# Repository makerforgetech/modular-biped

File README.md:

# Open Source, 3D Printable, Modular Robot Project

The **Modular Robot** project aims to educate and inspire individuals interested in robotics and electronics. This open-source initiative focuses on creating a fully autonomous companion robot with a variety of advanced features.

## Key Features

- **Control Systems**: Utilizes Arduino and Raspberry Pi, managed through custom PCBs.
- **Modular Body**: Configurable body components allow for easy customization and adaptability.
- **Software Modules**:
  - Animation: Handles the animation of the robot, including walking, turning, and other movements.
  - Braillespeak: Converts text to Braille and speaks it using a proprietary audio output using the onboard buzzer.
  - Buzzer: Controls the buzzer for audio output. Includes the ability to play tones and melodies.
  - ChatGPT: Uses the OpenAI GPT models to process text based on user input.
  - Logging: Logs data to a file for debugging and analysis.
  - Motion Detection: Handles motion detection using an onboard microwave motion sensor.
  - Neopixel: Controls the onboard Neopixel LEDs for visual feedback.
  - PiServo: Controls the servos connected to the Raspberry Pi.
  - PiTemperature: Reads the temperature from the integrated temperature sensor on the Raspberry Pi.
  - RTLSDR: Uses an RTL-SDR dongle to receive and process radio signals.
  - Serial Connection: Handles serial communication between the Raspberry Pi and Arduino.
  - Servos: Controls the servos connected to the Arduino via the Raspberry Pi and the serial connection.
  - Tracking: Uses computer vision to track objects and faces using the onboard camera.
  - Translator: Translates text between languages using the Google Translate API.
  - TTS: Converts text to speech using the onboard speaker.
  - Viam: Uses the VIAM API to integrate Viam modules for additional functionality.
  - Vision: Handles image processing and computer vision tasks using the onboard IMX500 Raspberry Pi AI camera.
  - Voice Recognition: Uses the Google Speech API to convert speech to text.
  - [Read more](https://github.com/makerforgetech/modular-biped/wiki/Software#modules)!

## Project Background

The Modular Robot Project is designed to provide a flexible and modular framework for robotics development using Python and C++ on the Raspberry Pi and Arduino platforms. It aims to enable developers, robotics enthusiasts, and curious individuals to experiment, create, and customize their own robots. With a range of features and functionalities and the option to add your own easily, the Modular Robot Project offers an exciting opportunity to explore the world of robotics.

## Modularity

The open source framework is designed for flexibility, allowing users to easily add or remove components to suit their specific needs. Comprehensive [guides](https://github.com/makerforgetech/modular-biped/wiki/Software#creating-a-module) are provided for integrating new modules seamlessly.

## Resources

- **Documentation**: For detailed information, visit the project’s GitHub wiki: [Modular Robot Documentation](https://github.com/makerforgetech/modular-biped/wiki)
- **Code**: Check out the modular open source software on [GitHub](https://github.com/makerforgetech/modular-biped)
- **YouTube Playlist**: Explore the development process through our build videos: [Watch on YouTube](https://www.youtube.com/watch?v=2DVJ5xxAuWY&list=PL_ua9QbuRTv6Kh8hiEXXVqywS8pklZraT)
- **Community**: Have a question or want to show off your build? Join the communities on [GitHub](https://bit.ly/maker-forge-community) and [Discord](https://bit.ly/makerforge-community)!

## A Note On Branches

The `main` branch is the latest stable release of the Modular Robot project. This is compatible with the 'buddy' release, the latest supported release.

The `develop` branch is the development branch and may contain experimental features and changes that are not yet stable. Please use the `main` branch for the most stable experience. This will eventually become the next release, 'cody'. To facilitate testing modules are disabled by default in the `develop` branch. Enable each as needed in the config yaml files to test.

## Modules

The 'Cody' release includes a new BaseModule class that must be extended by all modules. This class provides a common interface for all modules to interact with the main robot controller. The BaseModule class includes a messaging_service object that references the main robot controller's messaging service. This object is used to send and receive messages between modules and the main robot controller.

Both `pypubsub` and `paho-mqtt` can be used to facilitate message passing between modules (mqtt support is not implemented yet). Which service is used can be set in the messaging_service configuration YAML file.

```yaml
messaging_service:
  enabled: true
  config:
    protocol: 'pubsub' # 'mqtt' or 'pubsub'
    mqtt_host: 'localhost' 
    mqtt_port: 1883
```

The introduction of mqtt allows distributed communication between modules, even across different devices.

The methods publish() and subscribe() can be utilised from within any module to send and receive messages to topics.

For example:
  
  ```python
  class MyModule(BaseModule):
    def __init__(self):
        # Don't subscribe here
        pass
    
    def setup_messaging(self):
        """Subscribe to necessary topics."""
        self.subscribe('my_topic', self.my_callback)
        
    def my_callback(self, message):
        print(f'Received message: {message}')
        self.publish('my_response_topic', 'Hello from MyModule!')
        self.log(level='info', message='MyModule received a message!')
  ```
Core and common topics include:
- `log` - Used for logging messages, accepts a string. or kwargs `type` (info by default) and `message`.
- `log/info` - Used for logging informational messages.
- `log/warning` - Used for logging warning messages.
- `log/error` - Used for logging error messages.
- `log/debug` - Used for logging debug messages.
- `log/critical` - Used for logging critical messages. 
- `system/loop` - The main loop event. Subscribe to this for an action to trigger every loop.
- `system/loop/1` - Triggers a loop every second.
- `system/loop/10` - Triggers a loop every 10 seconds.
- `system/loop/60` - Triggers a loop every 60 seconds.
- `system/loop/exit` - Triggers a loop exit event.
- `system/temperature` - The current temperature of the Pi.
- `motion` - Output from the motion sensor, only triggered if motion is detected.
- `speech` - Input from speech recognition module converted to text.
- `tts` - Output to be spoken by the TTS module.
- `animate` - Output to be animated by the Animation module.
- `vision/detections` - Output from the Vision module, containing detected objects.
- `led` - Output to the Neopixel LED module.

## Logging

An upgraded log manager has been included in this version. This allows logs to be published either via the above messaging service, or directly to a 'log' method within the BaseModule class. The log manager can be configured in the `logwrapper.yaml` file.

```yaml
logwrapper:
  enabled: true # Highly recommended to enable this module
  path: modules.logwrapper.LogWrapper
  config:
    filename: app.log
    log_level: 'debug' # debug, info, warning, error, critical
    cli_level: 'info' # debug, info, warning, error, critical
  dependencies:
    python:
      - pypubsub
```

Both the log level of the app.log file and the output to the CLI during runtime can be determined and defined separately. For any log level set, logs of a level equal to or above that level will be output. For example, if the log level is set to 'info', all logs of level 'info', 'warning', 'error', and 'critical' will be output.

Example usage:

```python
class MyModule(BaseModule):
    def my_method(self):
        self.log(level='info', message='MyModule has been initialised!')
        self.log(f"Current value: {value}")
        self.log(message=f"Current value is too high: {value}", level='critical')
```

In addition, for modules that extend BaseModule, the class, method and line number are prefixed to the message for output, making it easier to track down where the log was generated.

```
log/info: [Personality.random_neopixel_status:117] [Personality] Neopixel status triggered set to green
log/info: [PiTemperature.monitor:30] Temperature: 45.5°C
log/critical: [PiTemperature.monitor:28] Temperature is critical: 45.5°C
```

The app.log also includes timestamps and log levels for easy reference.

```
INFO: 01/30/2025 12:05:26 PM [Main] Loop started using pubsub protocol
INFO: 01/30/2025 12:05:27 PM [Personality.random_neopixel_status:117] [Personality] Neopixel status triggered set to green
INFO: 01/30/2025 12:05:27 PM [PiTemperature.monitor:30] Temperature: 42.2°C
INFO: 01/30/2025 12:05:28 PM [PiTemperature.monitor:30] Temperature: 42.2°C
INFO: 01/30/2025 12:05:28 PM [Main] Loop ended
```

# Getting Started

1. Clone the repository and navigate to the project directory.
2. Review the environment configuration files in the `environments` folder and create your own if needed.
3. Run install.sh <environment> to set up the necessary dependencies and configurations for your chosen environment.
4. Add any environment variables required to /home/$USER/.myenv (this file is sourced on startup to set environment variables for the session).
5. Test by running startup.sh to start the robot. You should see logs in the CLI and app.log file indicating that the robot is running.
6. Ctrl+C to stop the robot.
7. To enable autolaunch on boot, run `./installers/autolaunch.sh enable <environment>` (defaults to laptop if no environment specified). To disable autolaunch, run `./installers/autolaunch.sh disable`.

# Adding New Modules
To add a new module, create a new directory in the `src/modules` directory with the name of your module. 

Inside this directory, create a Python file with the same name as the directory. This file should contain a class that extends the BaseModule class. 

Implement the necessary methods and functionality for your module. 

- `__init__(self, config, messaging_service)`: Initialize your module and set up any necessary variables or connections. The `config` parameter contains the configuration for your module from the YAML
- `setup_messaging(self)`: Set up any necessary subscriptions to topics using the `subscribe` method from the BaseModule class. You can subscribe to other topics or system/loop/<interval> for timed loops. See the wiki for more details on the messaging service and available topics.
- `loop(self)`: Implement the looping functionality of your module in this method. This method will be called repeatedly in the main loop of the robot.
- `__exit__(self)`: Clean up any resources or connections when the module is stopped. 

Create a configuration YAML file for your module in the new module's directory called `config.yml`. This file should include the class name of your module and any dependencies it requires, as well as any non-environment specific configuration.

```yaml
bno055:
  class: BNO055
  config:
    some_config: <this will be passed to the module's init method via kwargs>
  dependencies:
    python:
      - adafruit-circuitpython-bno055
      - adafruit-blinka
```

Finally, add your module to the configuration YAML file for your environment to enable it. 

You may wish to include environment specific configuration in the environment YAML file, which will be passed to the module's init method via kwargs.

```yaml
bus_servo:
  enabled: true
  config:
    poses:
      - legs_forward: {leg_r_tilt: 2806, leg_r_hip: 1989, leg_r_knee: 1349, leg_r_ankle: 2754, neck_pan: 1698, neck_tilt: 118, leg_l_tilt: 1619, leg_l_hip: 1028, leg_l_knee: 2634, leg_l_ankle: 1567}
  instances:
    - name: leg_r_tilt
      model: ST3215
      id: 1
      range: [2511, 3944]
      range_degrees: 125.9
      start: 2810
    - name: leg_r_hip
      model: ST3215
      id: 3
      range: [0, 2063]
      range_degrees: 181.3
```

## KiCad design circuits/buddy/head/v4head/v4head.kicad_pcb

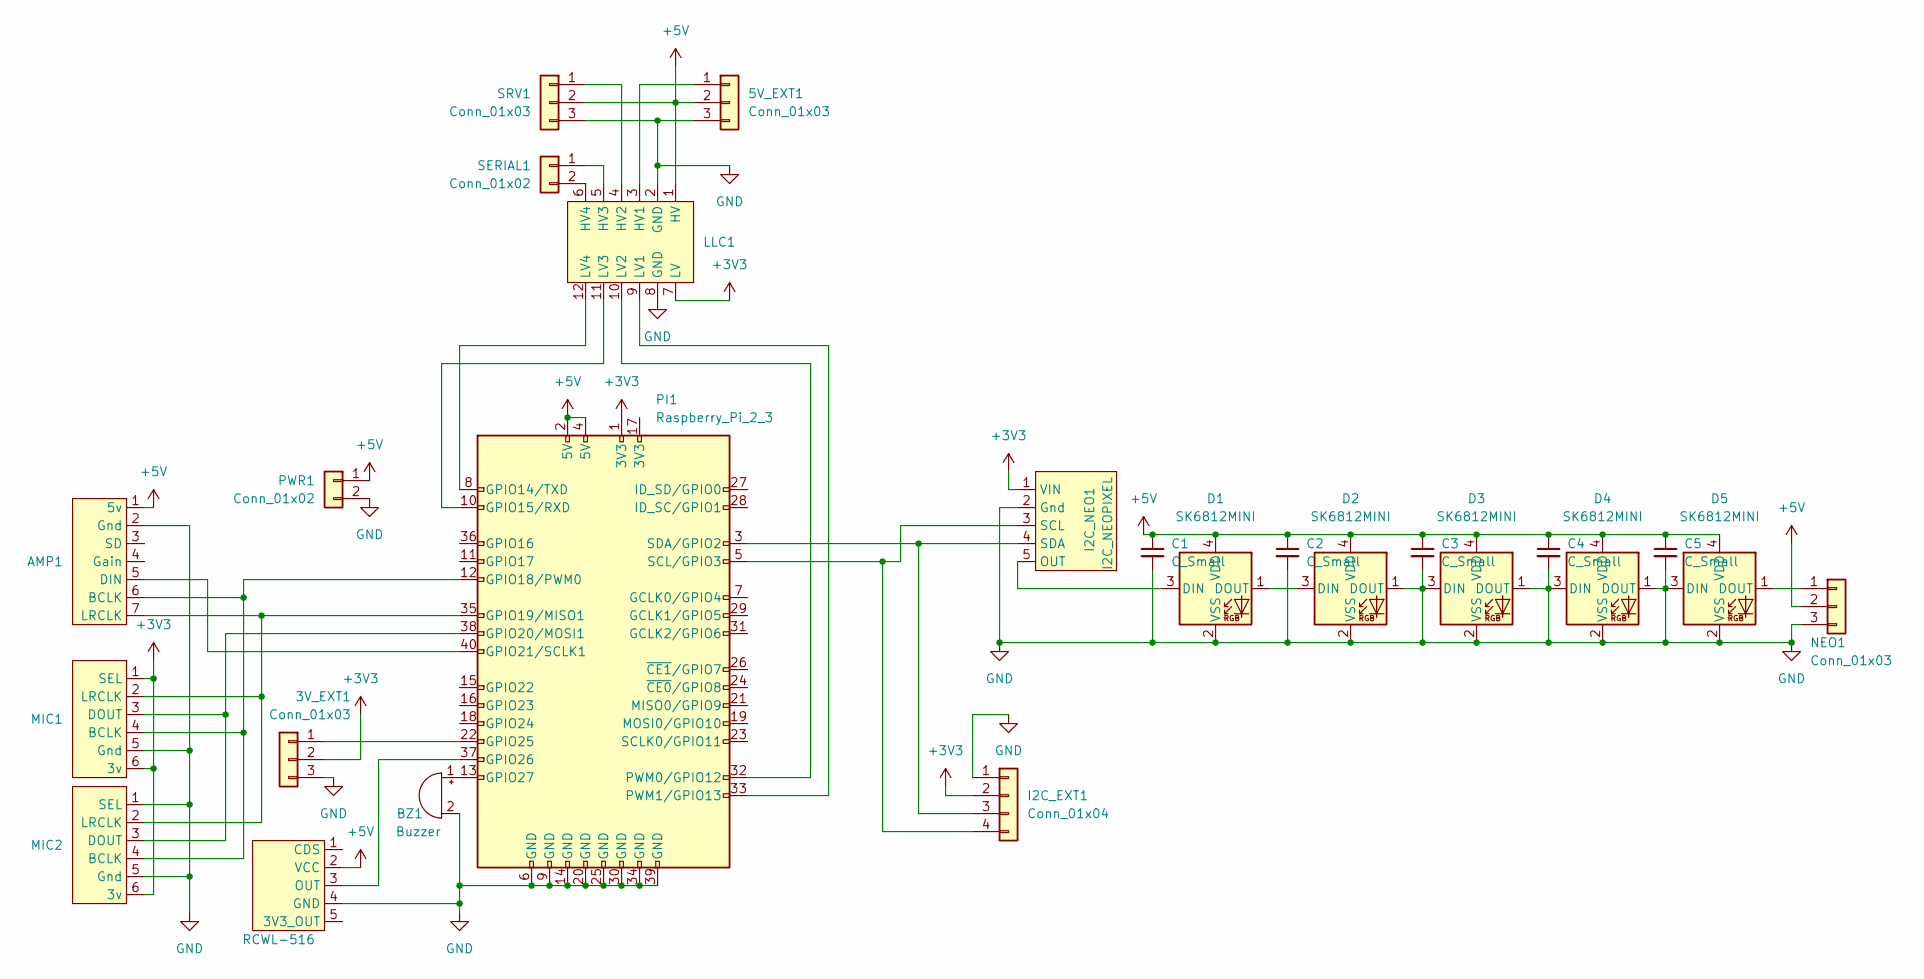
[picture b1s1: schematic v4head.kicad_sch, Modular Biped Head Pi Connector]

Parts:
3V_EXT1, 5V_EXT1: Conn_01x03; JST_XH_B3B-XH-A_1x03_P2.50mm_Vertical
AMP1: MAX98357
BZ1: Buzzer; Buzzer_12x9.5RM7.6
C1, C2, C3, C4, C5: C_Small; C_0201_0603Metric
D1, D2, D3, D4, D5: SK6812MINI; LED_SK6812MINI_PLCC4_3.5x3.5mm_P1.75mm
I2C_EXT1: Conn_01x04; JST_XH_B4B-XH-A_1x04_P2.50mm_Vertical
I2C_NEO1: I2C_NEOPIXEL
LLC1: LCC_BIDIRECTIONAL
MIC1, MIC2: SPH0645LM4H
NEO1: Conn_01x03; JST_XH_B3B-XH-A_1x03_P2.50mm_Vertical
PI1: Raspberry_Pi_2_3; PinHeader_2x20_P2.54mm_Vertical
PWR1: Conn_01x02; JST_XH_B2B-XH-A_1x02_P2.50mm_Vertical
RCWL-516: RCWL-0516_MIN
SERIAL1: Conn_01x02; JST_XH_B2B-XH-A_1x02_P2.50mm_Vertical
SRV1: Conn_01x03; PinHeader_1x03_P2.54mm_Vertical

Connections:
+3V3: 3V_EXT1.2, I2C_EXT1.2, I2C_NEO1.1 (VIN), LLC1.7 (LV), MIC1.1 (SEL), MIC1.6 (3v), MIC2.6 (3v), PI1.1 (3V3)
+5V: 5V_EXT1.2, AMP1.1 (5v), C1.1, C2.1, C3.1, C4.1, C5.1, D1.4 (VDD), D2.4 (VDD), D3.4 (VDD), D4.4 (VDD), D5.4 (VDD), LLC1.1 (HV), NEO1.2, PI1.2 (5V), PI1.4 (5V), PWR1.1, RCWL-516.2 (VCC), SRV1.2
GND: 3V_EXT1.3, 5V_EXT1.3, AMP1.2 (Gnd), BZ1.2 (+), C1.2, C2.2, C3.2, C4.2, C5.2, D1.2 (VSS), D2.1 (DOUT), D2.2 (VSS), D3.1 (DOUT), D3.2 (VSS), D3.3 (DIN), D4.1 (DOUT), D4.2 (VSS), D4.3 (DIN), D5.2 (VSS), D5.3 (DIN), I2C_EXT1.1, I2C_NEO1.2 (Gnd), LLC1.2 (GND), LLC1.8 (GND), MIC1.5 (Gnd), MIC2.1 (SEL), MIC2.5 (Gnd), NEO1.3, PI1.6 (GND), PI1.9 (GND), PI1.14 (GND), PI1.20 (GND), PI1.25 (GND), PI1.30 (GND), PI1.34 (GND), PI1.39 (GND), PWR1.2, RCWL-516.4 (GND), SRV1.3
unnamed: 3V_EXT1.1, PI1.22 (GPIO25)
unnamed: 5V_EXT1.1, LLC1.3 (HV1)
unnamed: AMP1.6 (BCLK), MIC1.4 (BCLK), MIC2.4 (BCLK), PI1.12 (GPIO18/PWM0)
unnamed: AMP1.5 (DIN), PI1.40 (GPIO21/SCLK1)
unnamed: AMP1.7 (LRCLK), MIC1.2 (LRCLK), MIC2.2 (LRCLK), PI1.35 (GPIO19/MISO1)
unnamed: BZ1.1 (-), PI1.13 (GPIO27)
unnamed: D1.3 (DIN), I2C_NEO1.5 (OUT)
unnamed: D1.1 (DOUT), D2.3 (DIN)
unnamed: D5.1 (DOUT), NEO1.1
unnamed: I2C_EXT1.3, I2C_NEO1.4 (SDA), PI1.3 (SDA/GPIO2)
unnamed: I2C_EXT1.4, I2C_NEO1.3 (SCL), PI1.5 (SCL/GPIO3)
unnamed: LLC1.4 (HV2), SRV1.1
unnamed: LLC1.5 (HV3), SERIAL1.1
unnamed: LLC1.6 (HV4), SERIAL1.2
unnamed: LLC1.9 (LV1), PI1.33 (PWM1/GPIO13)
unnamed: LLC1.10 (LV2), PI1.32 (PWM0/GPIO12)
unnamed: LLC1.11 (LV3), PI1.10 (GPIO15/RXD)
unnamed: LLC1.12 (LV4), PI1.8 (GPIO14/TXD)
unnamed: MIC1.3 (DOUT), MIC2.3 (DOUT), PI1.38 (GPIO20/MOSI1)
unnamed: PI1.37 (GPIO26), RCWL-516.3 (OUT)

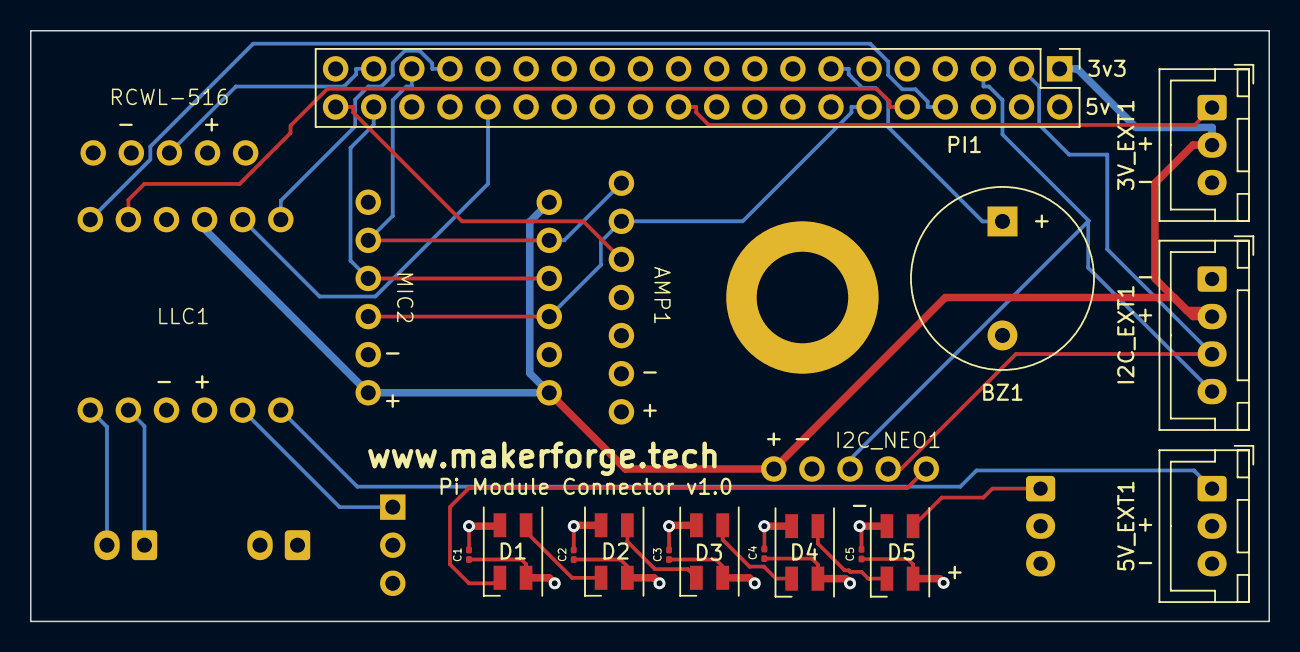
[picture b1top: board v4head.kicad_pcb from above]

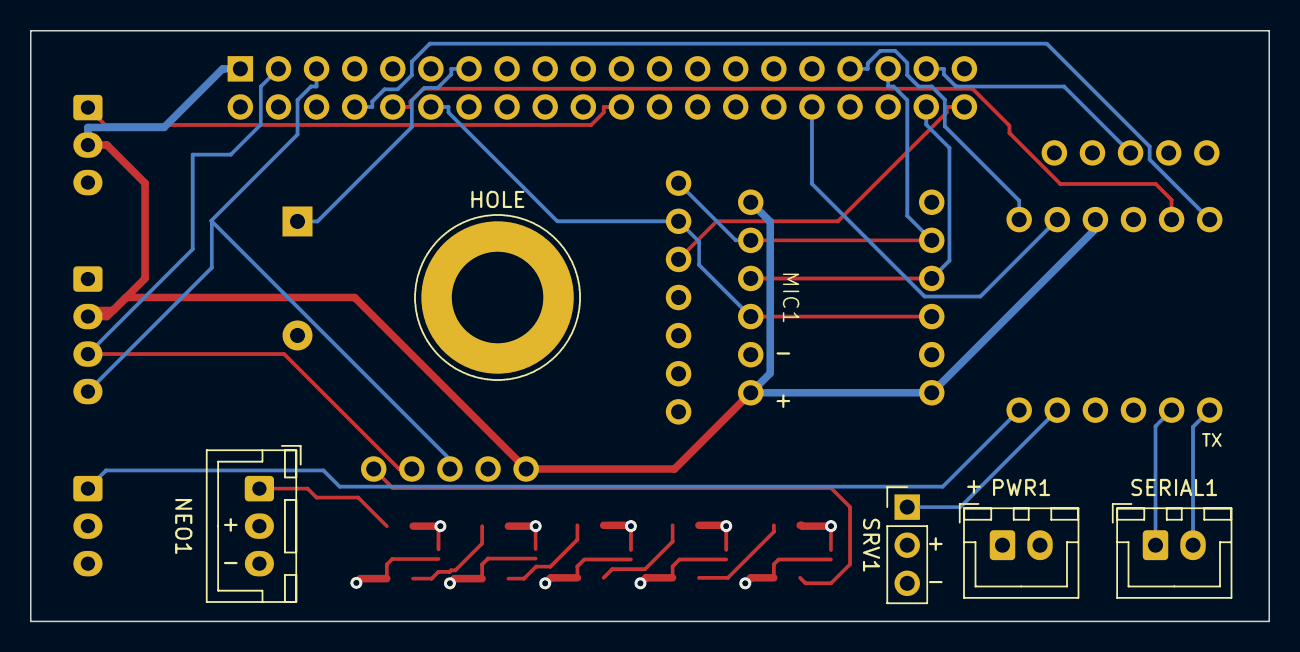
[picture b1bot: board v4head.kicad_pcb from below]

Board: 4 copper layers, 82.5 x 39.4 mm, 26 parts (6 on the bottom side), 23 nets.

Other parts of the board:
HOLE: Banana_Jack_1Pin

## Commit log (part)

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2023-04-08 Reposition legs so that forward knee is no longer used
2023-04-08 Calibrate legs
2023-04-22 Calibrate to new PCB
2023-05-13 Fix PCB
2023-05-13 Adjust PCB
2023-05-16 Refactor
2023-05-18 Adjustments
2023-05-27 Update circuits
2023-05-27 add image
2023-05-27 Image
2023-05-28 Adjust leg compensation
2023-05-29 Basic communication working. Needs reconfiguring all pi servo positions
2023-05-29 Disable any leg animations and remove references to third neck servo
2023-05-30 Trigger single servo movement in sleep mode
2023-05-30 Absolute servo movement in place
2023-06-01 Attempt to fix relative position
2023-06-02 Fix relative position animations
2023-06-02 Reduce log spamming and increase debounce time on tracking
2023-06-02 Remove test code
2023-07-18 Re-enable animations
2023-07-19 RFID.py Güncellendi
2023-07-20 Improved vision
2023-07-20 faces.py Güncellendi
    Gelişmiş görüş için Güncellendi
2023-07-20 feel.py Güncellendi
    Gelişmiş görüş için güncellendi
2023-07-20 tracking.py Güncellendi
    Gelişmiş görüş için güncellendi
2023-07-20 vision.py Güncellendi
    Gelişmiş görüş için güncellendi
2023-07-20 led.py Güncellendi
    Gelişmiş görüş için güncellendi
2023-07-20 pitemperature.py Güncellendi
    Gelişmiş görüş için güncellendi
2023-07-20 speechinput.py Güncellendi
    Gelişmiş görüş için güncellendi
2023-07-20 main.py Güncellendi
    Gelişmiş görüş için güncellendi
2023-07-20 Orjinal repo için oluşturduğum modüller yüklendi
2023-07-21 Handle object detection and face detection switching
2023-07-21 objects.py Eklendi
    Gelişmiş görüş için objeleri algılama modülü eklendi
2023-07-21 Shorten output sound
2023-07-21 Cleanup
2023-07-22 chatbot.py Güncellendi
2023-07-22 main.py Güncellendi
2023-07-22 chatbot.py silindi
2023-07-22 modules/chatbot klasörü silindi
2023-07-22 stop.sh Güncellendi
2023-07-22 startup.sh Güncellendi
2023-07-22 shutdown_pi.py Güncellendi
2023-07-22 preview_startup.sh Güncellendi
2023-07-22 manual_startup.sh Güncellendi
2023-07-24 WIP: Support audio output instead of neopixels
2023-07-28 tts.py Güncellendi
2023-07-28 WIP: Config as YAML files instead of python
2023-07-28 Migrate references to yaml (untested)
2023-07-29 Add documentation to yaml
2023-07-29 Added translator and attached to logger
2023-07-29 Debug
2023-07-29 Tested and fixed
2023-07-29 Set default language
2023-07-29 Disable speech recognition to debug
2023-07-29 Fix issues after testing
2023-07-29 requirements.txt Güncellendi
2023-07-29 config.py Güncellendi
2023-07-29 led.py Güncellendi
2023-07-29 logwrapper.py Güncellendi
2023-07-29 konfigürasyon için yml dosyaları eklendi
2023-07-29 Improved tracking
2023-07-31 Neopixel over i2c
2023-07-31 Disable debug on vision
2023-07-31 Include dependencies
2023-07-31 Rename module
2023-07-31 Modularisation
2023-08-01 vision.yml Güncellendi
2023-08-01 i2cneopixel.py eklendi
2023-08-01 tracking.py Güncellendi
2023-08-01 vision.py Güncellendi
2023-08-01 faces.py Güncellendi
2023-08-01 speechinput.py Güncellendi
2023-08-01 translator.py Güncellendi
2023-08-01 arduino_sketch.ino Güncellendi
2023-08-01 README.md Güncellendi
2023-08-04 Tilt hips to balance MPU6050 readings
2023-08-05 (W.I.P) mpu6050ve processing kodları yüklendi
    Hip balancing and processing codes are loaded with mpu6050 which is under development
2023-08-05 mpu6050.cpp eklendi
2023-08-05 SentryBOT.stl ve SentryBOT.glb eklendi
2023-08-09 Geliştirme Aşamasında Eklentiler klasörü silindi
2023-08-09 mpu6050 ve processing integrasyonu
2023-08-09 processing.java güncellendi
2023-08-09 botModel.3mf yüklendi bunu .obj'ye dönüştürün
    Since the file in .obj format exceeds the upload limit, I uploaded it in 3mf format. You can save it as in the 3d builder that comes with windows and convert it to obj format
2023-08-09 Completed v1 of MPU6050 support
2023-08-19 chataigpt.py oluşturuldu
2023-08-19 chataigpt.py ingil
2023-08-19 chataigpt.py ingilizce çevrildi
2023-08-19 chataigpt.py anadili ingilizce olarak ayarlandı
2023-08-19 chataigpt.py .yml konumu güncellendi
2023-09-13 Fix develop branch
2023-09-17 Config.h Güncellendi
2023-09-17 Mpu6050.h eklendi
2023-09-17 Order.h Güncellendi
2023-09-17 ServoManager.h Güncellendi
2023-09-17 Ad değişikliği
2023-11-01 First pass at new PCB for head
2023-11-11 Disable test code
2023-11-16 Updates to circuit
2023-11-16 Swap TX & RX to align with LLC
2023-11-16 Update annotations
2023-11-17 Final version 1.0. Added decoupling caps to neopixels.
2023-11-17 Added version number
2023-11-17 Save
2023-12-16 Stable on Pi 5. Disabled modules with issues temporarily. Created sentiment analysis behaviour
2023-12-22 Make eye glow when using camera
2024-01-02 Limit animation range
2024-01-02 Init changes
2024-01-11 Test viam logging
2024-01-12 Added logs to main_viam
2024-01-16 Add test process
2024-03-11 Latest changes on sketch
2024-03-11 Servo adjust
2024-03-13 Fix pi movements and animations
2024-03-16 Head shake on wake
2024-04-21 Resolve and update conflict in NeoPx.py
2024-04-21 Update neopixel.yml to resolve conflict
2024-04-21 Quotation errors in VsCode auto editing have been updated
2024-04-21 Disable viam install
2024-05-10 Improvements, backpack + restraining bolt support
2024-05-13 Fixes
2024-05-22 Testing viam
2024-10-04 Latest updates
2024-10-04 Assistant test script
2024-10-04 Initial commit of assistant (untested)
2024-10-04 remove json file
2024-10-05 Added animations and tested on laptop
2024-10-05 Rename emotion_analysis_module.py to emotion_analysis.py
2024-10-05 Clean up
2024-10-05 Testing
2024-10-14 No need to flip
2024-10-14 Ensure venv can access neopixel packages
2024-10-14 Allow manual selection of serial port
2024-10-14 Rough rework to fit module format
2024-10-18 Fixed to allow boot
2024-10-18 Rough first integration. Needs finetuning
2024-10-18 Improve visibility of distance to center of camera
2024-10-20 Fine tuning
2024-10-20 Adjust config
2024-10-23 Calibrating X, disabled Y
2024-10-26 Implemented dynamic modules. Archived untested modules.
2024-10-26 Implement dynamic viam module clients
2024-10-26 Refactor emotional analysis module
2024-10-26 Manage dependencies dynamically using config files
2024-10-27 Manage manual installation steps in install script
2024-10-27 Activate install
2024-10-28 SDR module
2024-10-29 Add image for wiki
2024-10-30 Update images
2024-10-30 Update image
2024-10-31 Add telegram module
2024-11-01 Update modules
2024-11-02 Battery Monitor
2024-12-06 Added CM5 Modules.drawio
2024-12-06 Added CM5 Modules.drawio.png
2024-12-06 Added CM5 Modules.drawio.svg
2024-12-20 Fixes to install (also applies to pi 5)
2024-12-30 Beginning of SPI support
2024-12-31 Successful test of SPI neopixels
2024-12-31 Remove unused file
2025-01-01 L298N Support & LED Flashlight
2025-01-01 Added Motor directions
2025-01-01 Clean up neopixel protocol selection
2025-01-01 Adjustments for buddy branch
2025-01-02 Initial successful test of I2S mic and speaker modules. Installers to support configuration
2025-01-02 Added basic i2c servo control. Successful test
2025-01-03 Successful TFT display test script
2025-01-03 Test servos
2025-01-03 MPU6050 test and sensor test
2025-01-06 Auto launch installer
2025-01-06 Adjustments during testing
2025-01-06 Re-add svg
2025-01-09 Added relay and code to enter servo motor sitting animation in OpenCV mode, ensuring only leg motors operate and preventing power consumption by the servo motors later."
2025-01-15 Added Software Architecture.drawio.svg
2025-01-27 Working speech recognition, GPT interpretation, and TTS output on CM5
2025-01-27 Clear lock on audio devices before running. Tweak config to allow for better recognition
2025-01-29 Move logger to module
2025-01-29 Creation of messaging service class. Pubsub tested
2025-01-29 WIP mqtt support
2025-01-30 Improved logging tool
2025-01-30 Remove unused depdendencies
2025-02-05 Add Ollama Module
2025-02-20 New vision method "remote vision " added
2025-02-22 Updated vision.yml for vision selection
2025-02-25 New feature Neopixel drive wtih Esp32
2025-02-26 New animations added
2025-02-27 Arguments updated and new animations added
2025-03-02 Remote vision and Ollama module update.
2025-03-08 ESP32 protocol test
2025-03-09 Added Neopixel driving protocol with Esp32/8266
2025-03-09 PR template
2025-03-09 Created unit test framework
2025-03-09 Fix version issue
2025-03-09 Fix test workflow
2025-03-09 simplify
2025-03-09 Pass
2025-03-09 Update tests
2025-03-10 Unit tests
2025-03-11 Clean up and docs
2025-03-11 fix test
2025-03-11 Rename
2025-03-14 Create 'legMode' to define different modes based on analog input from rotary pot
2025-03-16 Support leg mode selector
2025-03-16 Correct default mode
2025-03-17 Enable buddy configuration
2025-03-19 Clean up of logic and add feature flags
2025-03-21 Tested with rotary switch
2025-03-22 Fixes to vision and piServo
2025-06-08 Local override config files enabled
2025-12-21 Initial plan
2025-12-21 Change DEFAULT_SLEEP_INTERVAL to 0.01 (10ms)
2026-03-22 Correcct config for buddy and cody
2026-03-22 Tested Cody
2026-03-26 Improvements to bus servo library management
2026-03-26 Apply PR review feedback: fix waveshare backend, bus_servo, personality, and test files
    Agent-Logs-Url: https://github.com/makerforgetech/modular-biped/sessions/224876d0-40b3-4e56-9ccc-bbbfd5ed44a1
2026-03-27 Add _WaveshareConnectionManager: shared port/handler with ref-counting for same-bus servos
    Agent-Logs-Url: https://github.com/makerforgetech/modular-biped/sessions/ae8b758b-e5cb-4cc1-aabf-2c2c41aa5074
2026-03-29 Tested waveshare backend
2026-03-29 Introduce ServoManager for centralised bus servo control
    Agent-Logs-Url: https://github.com/makerforgetech/modular-biped/sessions/ac60dd13-c688-4151-b48b-7f769e416658
2026-04-07 feat: replace Personality with Companion module (state machine, AI pipeline, proactive greeting)
    Agent-Logs-Url: https://github.com/makerforgetech/modular-biped/sessions/2d9caed9-a110-4cce-bec7-d777b0917e69
2026-04-07 fix: consolidate display coordinate transform; improve test maintainability
    Agent-Logs-Url: https://github.com/makerforgetech/modular-biped/sessions/2d9caed9-a110-4cce-bec7-d777b0917e69
2026-04-11 WIP changes
2026-04-20 Fix bus servo moving-state mismatch handling
    Agent-Logs-Url: https://github.com/makerforgetech/modular-biped/sessions/4eafc430-617c-4c05-a2bd-ea0bc585fcc3
2026-04-20 Strengthen bus_servo warning assertion in tests
    Agent-Logs-Url: https://github.com/makerforgetech/modular-biped/sessions/4eafc430-617c-4c05-a2bd-ea0bc585fcc3
2026-04-20 Assert no warning when servo is within tolerance
    Agent-Logs-Url: https://github.com/makerforgetech/modular-biped/sessions/4eafc430-617c-4c05-a2bd-ea0bc585fcc3
2026-04-20 Share bus port handler across servos and serialize SDK access
    Agent-Logs-Url: https://github.com/makerforgetech/modular-biped/sessions/ce792005-8d16-4964-9853-5beedd8c2a79
2026-04-20 Harden shared port refcount close and SC center error handling
    Agent-Logs-Url: https://github.com/makerforgetech/modular-biped/sessions/ce792005-8d16-4964-9853-5beedd8c2a79
2026-04-20 Revert accidental WIP regressions blocking bus servo operation
    Agent-Logs-Url: https://github.com/makerforgetech/modular-biped/sessions/607e681f-29e0-49d9-98c9-db6a4e60d6e0
2026-04-20 Saved changes prior to AI screw up
2026-04-20 Stabilize bus servo comms with retry logic while keeping deliberate speed and moving semantics
    Agent-Logs-Url: https://github.com/makerforgetech/modular-biped/sessions/f2f37f5f-4b6d-4f4d-a1eb-415829fea05b
2026-04-23 Cleaner animation and pose changes. Carry detection
2026-04-23 Add on_load method to modules
2026-04-23 Prevent unwanted animation
2026-04-23 Fix neck_tilt overshoot: use SC_MAX for SC09 in calculate_range_degrees
    Agent-Logs-Url: https://github.com/makerforgetech/modular-biped/sessions/26bc1434-489e-4911-9d24-d558a59a046b
2026-04-23 Installer
2026-04-23 Resolve feedback
2026-04-23 Remove servo/pose topic
2026-05-20 Disable wave every 60 seconds
2026-05-21 Fixed audio and mic. Created voice recognition environment config
2026-05-22 feat: add RSVPDisplay module with full test coverage
    Agent-Logs-Url: https://github.com/makerforgetech/modular-biped/sessions/15755c1b-c43c-4a30-9e3c-d46e068bcba0
